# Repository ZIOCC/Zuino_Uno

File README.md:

# Zuino M Uno Microcontroller

> This product can be available for purchase [here](https://www.smart-prototyping.com/Zuino-M-UNO.html).

#### Description

Based on the ATmega328, this microcontroller is Arduino and Arduino Uno R3-compatible. Our version of this famously popular microcontroller board integrates a Qwiic connector at either end of the PCB, enabling it to be easily connected with other Qwiic-compatible modules.

The Arduino Uno is the board with which many makers get started. It’s comparatively inexpensive, easy to use, and open source. The worldwide collaborative community, coupled with the easy-to-use IDE, are the primary reasons this microcontroller is the nearly ubiquitous introduction to embedded computing for the last decade. 

This board comes with all of the functions and features that you know and love from the Arduino Uno, with the added bonus of on-board Qwiic capability. The familiar header pins will allow you to use it with any Arduino shield or other modules that lack a Qwiic connector.

Note: you cannot power the Zuino M Uno via Qwiic, as it is a 5v device, and does not include a 3.3v-to-5v boost converter.

#### Specification

* Microcontroller: Atmega328P
* Operating Voltage: 5V
* Input Voltage: 7-12V
* Digital I/O Pins: 14 (6 provide PWM output)
* PWM Digital I/O Pins: 6
* Analog Input Pins: 6
* DC Current per I/O Pin: 20 mA
* DC Current for 3.3V Pin and Qwiic: 50 mA
* Flash Memory: 32KB (0.5 KB is used by bootloader)
* SRAM: 2 KB
* EEPROM: 1 KB
* Clock Speed: 16 MHz
* Dimensions:
* Weight: 18.7g (0.66oz)

#### Links

* [PCB Source file](https://github.com/ZIOCC/Zuino_Uno)

> ###### About Zio
> Zio is a new line of open sourced, compact, and grid layout boards, fully integrated for Arduino and Qwiic ecosystem. Designed ideally for wearables, robotics, small-space limitations or other on the go projects. Check out other awesome Zio products [here](https://www.smart-prototyping.com/Zio).

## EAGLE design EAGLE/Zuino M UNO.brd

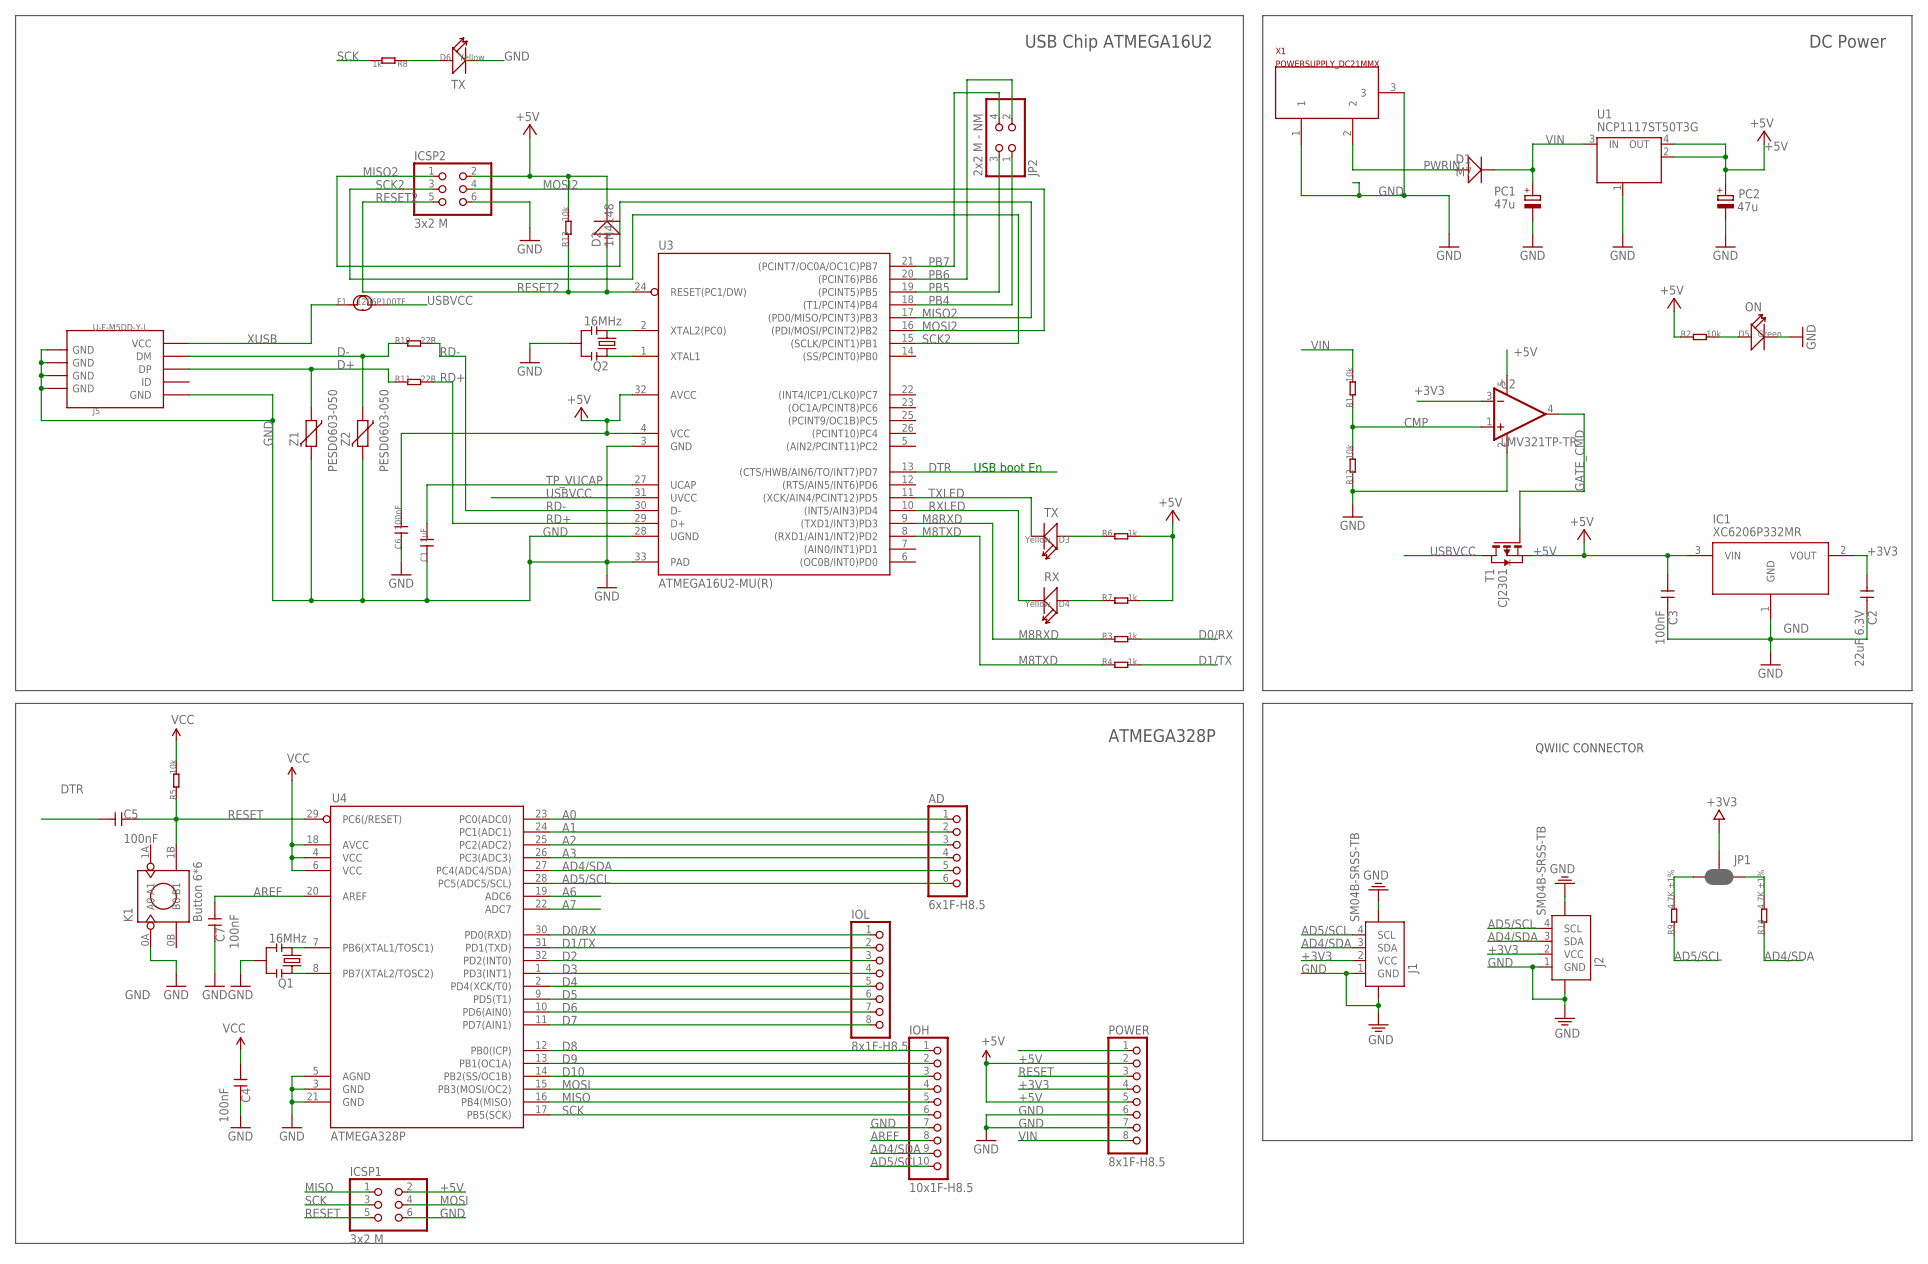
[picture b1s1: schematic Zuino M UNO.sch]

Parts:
AD: 6x1F-H8.5; 1X06
C1: 1uF; 0603
C2: 22uF 6.3V; 0603
C3, C4, C5, C6, C7: 100nF; 0603
D1: M7; SMA
D2: 1N4148; SOD123
D3, D4, D6: Yellow; LED-0805
D5: Green; LED-0805
F1: 1206P100TF; 1206
IC1: XC6206P332MR; SOT23
ICSP1, ICSP2: 3x2 M; 2X03
IOH: 10x1F-H8.5; 1X10
IOL: 8x1F-H8.5; 1X08
J1, J2: SM04B-SRSS-TB; JST-SH-4P
J5: U-F-M5DD-Y-L; MICRO-SMD
JP1: JUMPER-SMT_3_2-NC_PASTE_SILK; SMT-JUMPER_3_2-NC_PASTE_SILK
JP2: 2x2 M - NM; 2X02
K1: Button 6*6; 4P-SMD-6X6
PC1, PC2: 47u; PANASONIC_D
POWER: 8x1F-H8.5; 1X08
Q1, Q2: 16MHz; RESONATOR-SMD
R1, R2, R5, R12, R13: 10k; 0603
R3, R4, R6, R7, R8: 1k; 0603
R9, R14: 4.7K ±1%; 0603
R10, R11: 22R; 0603
T1: CJ2301; SOT-23
U1: NCP1117ST50T3G; SOT223
U2: LMV321TP-TR; SOT23-5
U3: ATMEGA16U2-MU(R); MLF32
U4: ATMEGA328P; TQFP32-08
X1: POWERSUPPLY_DC21MMX; POWERSUPPLY_DC-21MM
Z1, Z2: PESD0603-050; CT/CN0603

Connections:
+3V3: C2.1, IC1.2 (VOUT), J1.2 (VCC), J2.2 (VCC), JP1.2, POWER.4, U2.3 (IN-)
+5V: C3.1, C4.2, C6.2, D2.-, IC1.3 (VIN), ICSP1.2, ICSP2.2, PC2.+, POWER.2, POWER.5, R2.1, R5.2, R6.2, R7.2, R13.2, T1.2 (S), U1.2 (OUT), U1.4 (OUT), U2.5 (V+), U3.4 (VCC), U3.32 (AVCC), U4.4 (VCC), U4.6 (VCC), U4.18 (AVCC)
A0: AD.1, U4.23 (PC0(ADC0))
A1: AD.2, U4.24 (PC1(ADC1))
A2: AD.3, U4.25 (PC2(ADC2))
A3: AD.4, U4.26 (PC3(ADC3))
A6: U4.19 (ADC6)
A7: U4.22 (ADC7)
AD4/SDA: AD.5, IOH.9, J1.3 (SDA), J2.3 (SDA), R14.1, U4.27 (PC4(ADC4/SDA))
AD5/SCL: AD.6, IOH.10, J1.4 (SCL), J2.4 (SCL), R9.1, U4.28 (PC5(ADC5/SCL))
AREF: C7.2, IOH.8, U4.20 (AREF)
CMP: R1.1, R12.2, U2.1 (IN+)
D0/RX: IOL.1, R3.2, U4.30 (PD0(RXD))
D1/TX: IOL.2, R4.2, U4.31 (PD1(TXD))
D2: IOL.3, U4.32 (PD2(INT0))
D3: IOL.4, U4.1 (PD3(INT1))
D4: IOL.5, U4.2 (PD4(XCK/T0))
D5: IOL.6, U4.9 (PD5(T1))
D6: IOL.7, U4.10 (PD6(AIN0))
D7: IOL.8, U4.11 (PD7(AIN1))
D8: IOH.1, U4.12 (PB0(ICP))
D9: IOH.2, U4.13 (PB1(OC1A))
D10: IOH.3, U4.14 (PB2(SS/OC1B))
D+: J5.D+ (DP), R11.1, Z1.1
D-: J5.D- (DM), R10.1, Z2.1
DTR: C5.2, U3.13 ((CTS/HWB/AIN6/TO/INT7)PD7)
GATE_CMD: T1.3 (G), U2.4 (OUT)
GND: C1.1, C2.2, C3.2, C4.1, C6.1, C7.1, D5.-, D6.-, IC1.1 (GND), ICSP1.6, ICSP2.6, IOH.7, J1.1 (GND), J1.NC1 (5), J1.NC2 (6), J2.1 (GND), J2.NC1 (5), J2.NC2 (6), J5.GND, J5.S1 (GND), J5.S1@1 (GND), J5.S1@2 (GND), J5.S2 (GND), J5.S2@1 (GND), J5.S2@2 (GND), J5.S3 (GND), J5.S3@1 (GND), J5.S3@2 (GND), J5.S4 (GND), J5.S4@1 (GND), J5.S4@2 (GND), K1.0A (A0), PC1.-, PC2.-, POWER.6, POWER.7, Q1.2, Q2.2, R12.1, U1.1 (GND/ADJ), U2.2 (V-), U3.3 (GND), U3.28 (UGND), U3.33 (PAD), U4.3 (GND), U4.5 (AGND), U4.21 (GND), X1.1, X1.3, Z1.2, Z2.2
M8RXD: R3.1, U3.9 ((TXD1/INT3)PD3)
M8TXD: R4.1, U3.8 ((RXD1/AIN1/INT2)PD2)
MISO: ICSP1.1, IOH.5, U4.16 (PB4(MISO))
MISO2: ICSP2.1, U3.17 ((PD0/MISO/PCINT3)PB3)
MOSI: ICSP1.4, IOH.4, U4.15 (PB3(MOSI/OC2))
MOSI2: ICSP2.4, U3.16 ((PDI/MOSI/PCINT2)PB2)
unnamed: D6.+, R8.1
unnamed: D5.+, R2.2
unnamed: Q2.1, U3.1 (XTAL1)
unnamed: JP1.3, R9.2
unnamed: JP1.1, R14.2
unnamed: Q1.1, U4.8 (PB7(XTAL2/TOSC2))
unnamed: Q1.3, U4.7 (PB6(XTAL1/TOSC1))
unnamed: Q2.3, U3.2 (XTAL2(PC0))
unnamed: D4.+, R7.1
unnamed: D3.+, R6.1
PB4: JP2.1, U3.18 ((T1/PCINT4)PB4)
PB5: JP2.3, U3.19 ((PCINT5)PB5)
PB6: JP2.2, U3.20 ((PCINT6)PB6)
PB7: JP2.4, U3.21 ((PCINT7/OC0A/OC1C)PB7)
PWRIN: D1.P$2 (+), X1.2
RD+: R11.2, U3.29 (D+)
RD-: R10.2, U3.30 (D-)
RESET: C5.1, ICSP1.5, K1.1B (B1), POWER.3, R5.1, U4.29 (PC6(/RESET))
RESET2: D2.+, ICSP2.5, R13.1, U3.24 (RESET(PC1/DW))
RXLED: D4.-, U3.10 ((INT5/AIN3)PD4)
SCK: ICSP1.3, IOH.6, R8.2, U4.17 (PB5(SCK))
SCK2: ICSP2.3, U3.15 ((SCLK/PCINT1)PB1)
TP_VUCAP: C1.2, U3.27 (UCAP)
TXLED: D3.-, U3.11 ((XCK/AIN4/PCINT12)PD5)
USBVCC: F1.2, T1.1 (D), U3.31 (UVCC)
VIN: D1.P$1 (-), PC1.+, POWER.8, R1.2, U1.3 (IN)
XUSB: F1.1, J5.VBUS (VCC)

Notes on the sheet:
USB boot En
USB Chip ATMEGA16U2
ATMEGA328P
DC Power
QWIIC CONNECTOR

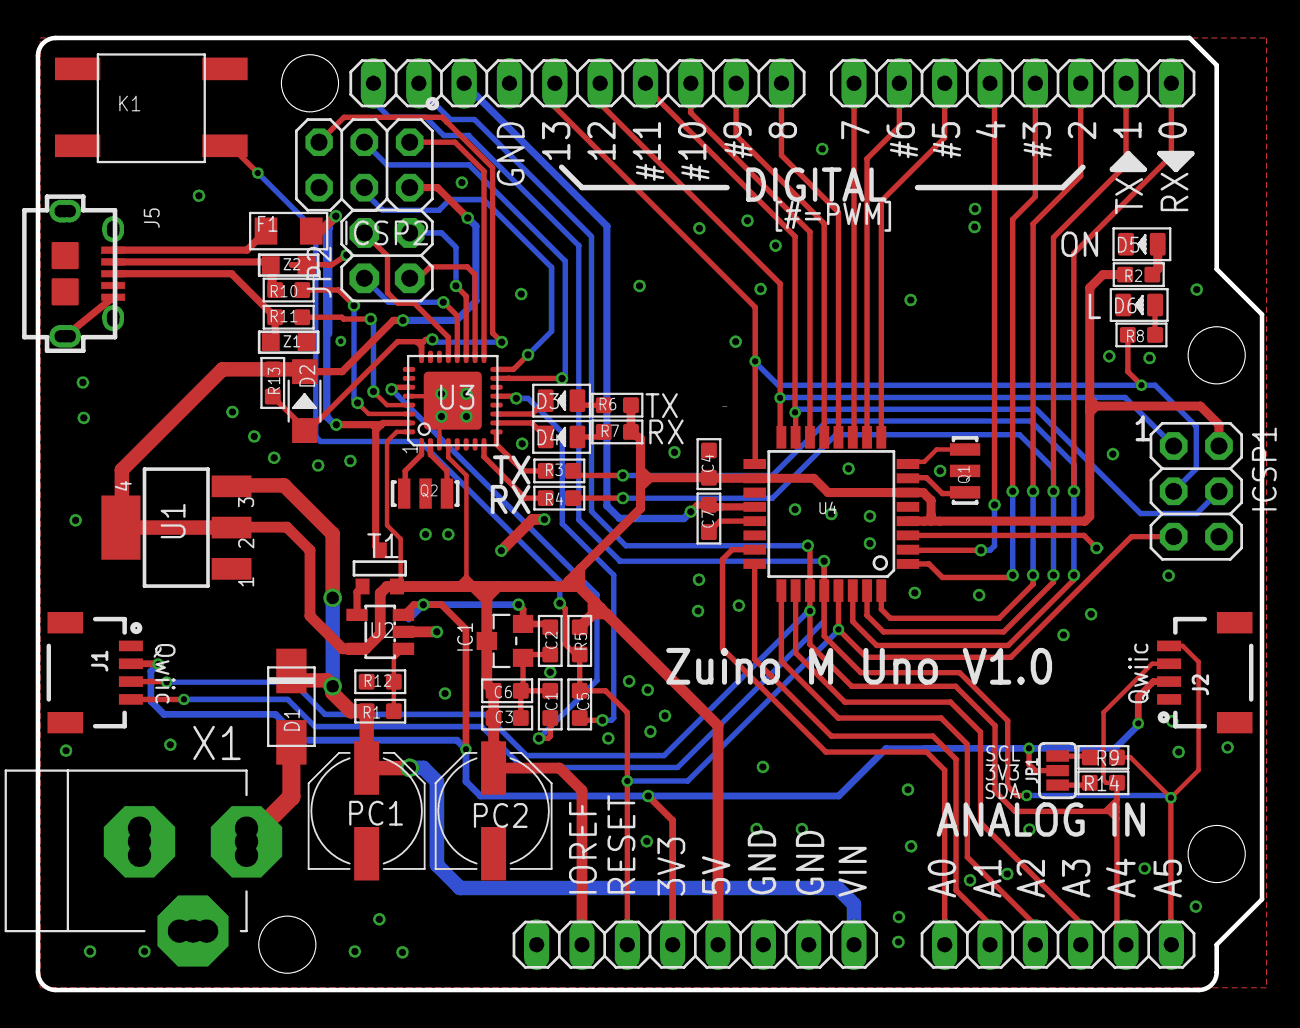
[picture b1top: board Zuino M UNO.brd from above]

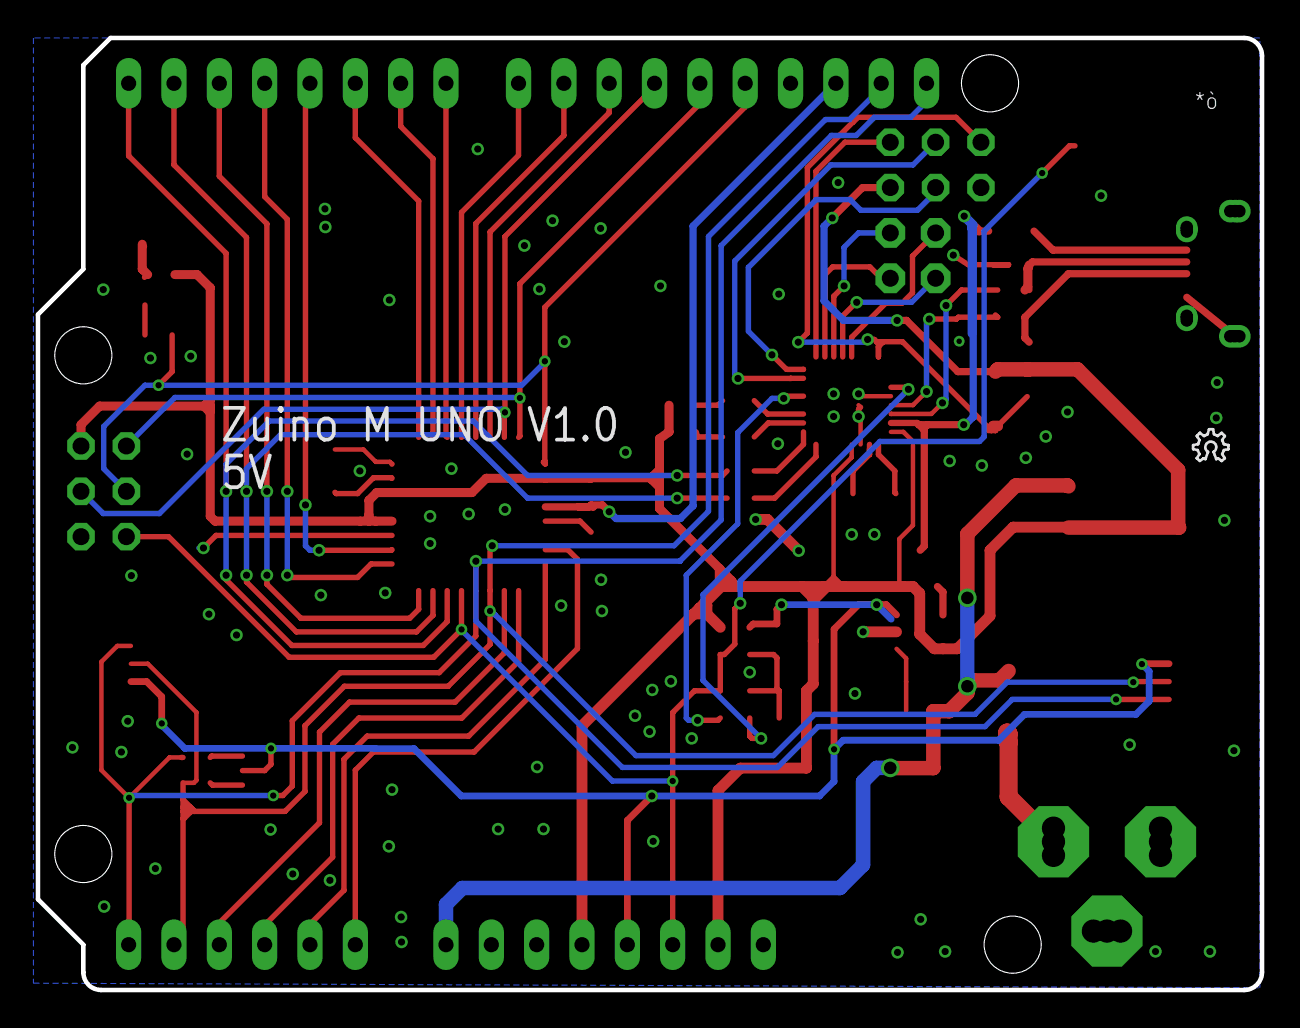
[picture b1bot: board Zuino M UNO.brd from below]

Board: 2 copper layers, 68.6 x 53.3 mm, 56 parts (2 on the bottom side), 59 nets.

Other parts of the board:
E$13: 12MM
LOGO1: LOGO-OSHW-6MILX0070-NT; OSHW_6X70_NOTEXT
U$1: 10MM

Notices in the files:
parts and their libraries:
SparkFun-Jumpers: Licensing: Creative Commons ShareAlike 4.0 International - https://creativecommons.org/licenses/by-sa/4.0
